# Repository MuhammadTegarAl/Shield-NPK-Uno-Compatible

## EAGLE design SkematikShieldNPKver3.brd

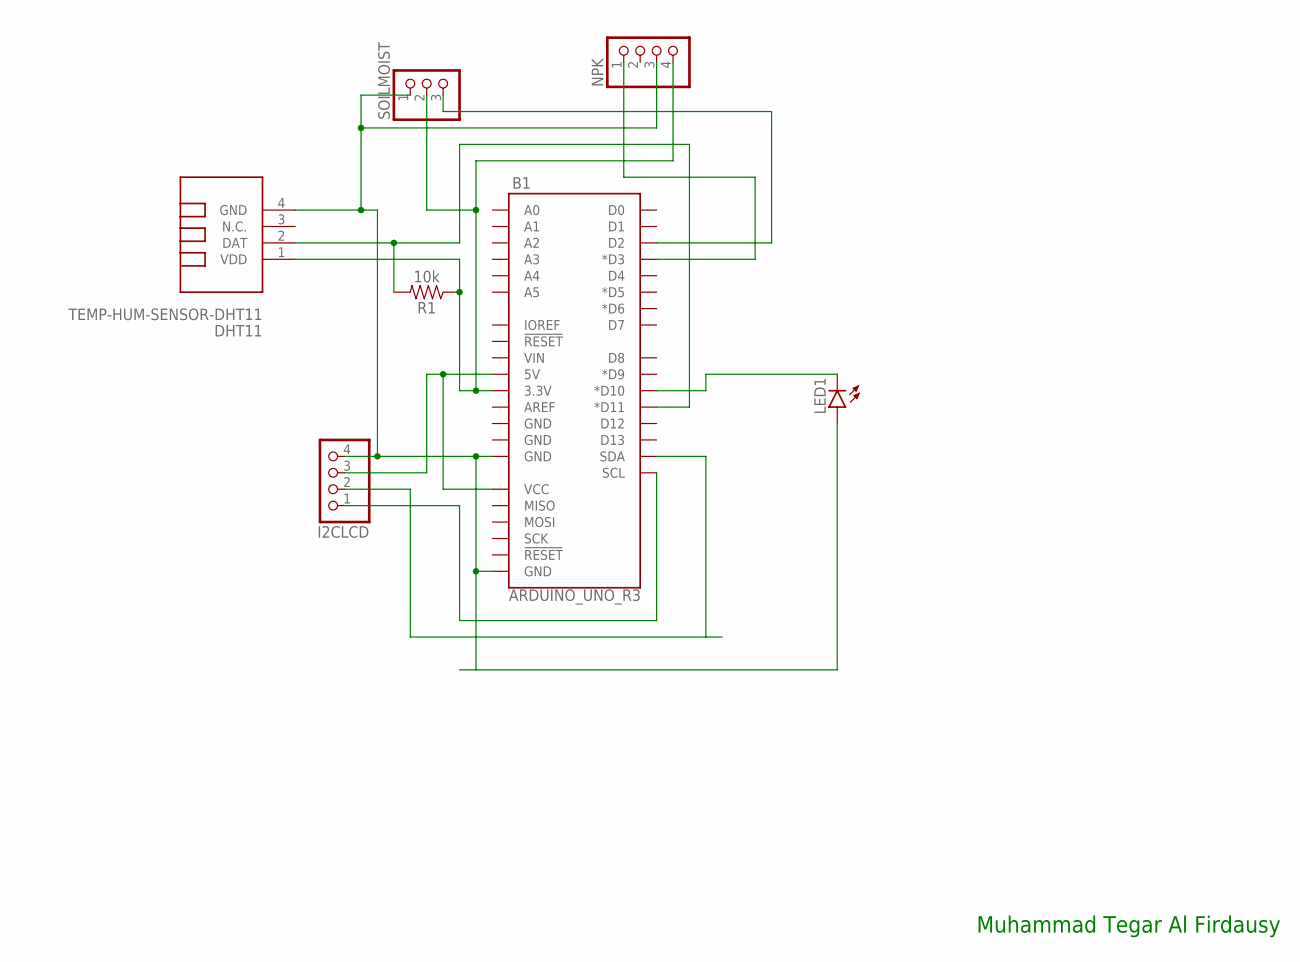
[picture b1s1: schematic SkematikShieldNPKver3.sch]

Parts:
B1: ARDUINO_UNO_R3; ARDUINO_R3
DHT11: TEMP-HUM-SENSOR-DHT11
I2CLCD: PINHD-1X4; 1X04
LED1: LED5MM
NPK: PINHD-1X4; 1X04
R1: 10k; AXIAL-0.3
SOILMOIST: PINHD-1X3; 1X03

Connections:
unnamed: B1.GND@1 (GND), B1.GND@2 (GND), DHT11.4 (GND), I2CLCD.4, LED1.A, NPK.3, SOILMOIST.1
unnamed: B1.5V, B1.VCC, I2CLCD.3
unnamed: B1.SDA, I2CLCD.2
unnamed: B1.SCL, I2CLCD.1
unnamed: B1.3.3V, DHT11.1 (VDD), NPK.4, R1.P$1 (1), SOILMOIST.2
unnamed: B1.D11 (*D11), DHT11.2 (DAT), R1.P$2 (2)
unnamed: B1.D2, SOILMOIST.3
unnamed: B1.D3 (*D3), NPK.1
unnamed: B1.D10 (*D10), LED1.K (C)

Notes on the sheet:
Muhammad Tegar Al Firdausy

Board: 2 copper layers, 7 parts (1 on the bottom side), 9 nets, no tracks yet.

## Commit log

2020-10-13 skematik sudah selsai, board design belum

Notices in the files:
parts and their libraries:
SparkFun-Boards: Licensing: Creative Commons ShareAlike 4.0 International - https://creativecommons.org/licenses/by-sa/4.0
diy-modules: Released under the Creative Commons Attribution 4.0 International License: http://creativecommons.org/licenses/by/4.0
